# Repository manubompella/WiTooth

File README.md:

# WiTooth

The WiTooth is based on Espressif ESP32 WiFi-BT-BLE SoC (System on Chip), ESP32 contains two low-power Xtensa® 32-bit LX6 microprocessors running at 80 MHz. Features include:

 * Integrated 802.11 BGN WiFi transceiver
 * Integrated dual-mode Bluetooth (classic and BLE)
 * Dual-core Tensilica LX6 microprocessor
 * Up to 240MHz clock frequency
 * 520kB internal SRAM
 * 10-electrode capacitive touch support
 * Hardware accelerated encryption (AES, SHA2, ECC, RSA-4096)
 * 2.2 to 3.6V operating range
 * 2.5 µA deep sleep current
 * 3 SPI, 2 I2C, 2 UART
 * 16 PWM outputs
 * 2 DAC
 * 2 I2S
 * 18 analog-to-digital converter (ADC) channels
 
## Platform Features

 * Compatible with Arduino IDE
 * USB powered
 * CP2102 USB-to-UART Bridge
 * Extended breadboard compatible headers
 * UART, SPI, I2C
 * On-board RESET
 
## Maintainers

The WiTooth is maintained by thingTronics Innovations.

Main contributor:
 * Manohar Bompella@<manohar.bompella@thingtronics.com>
 * Poornima Nagesh @<poornima.nagesh@thingtronics.com>
 * Lovelesh Patel @<lovelesh.patel@thingtronics.com>

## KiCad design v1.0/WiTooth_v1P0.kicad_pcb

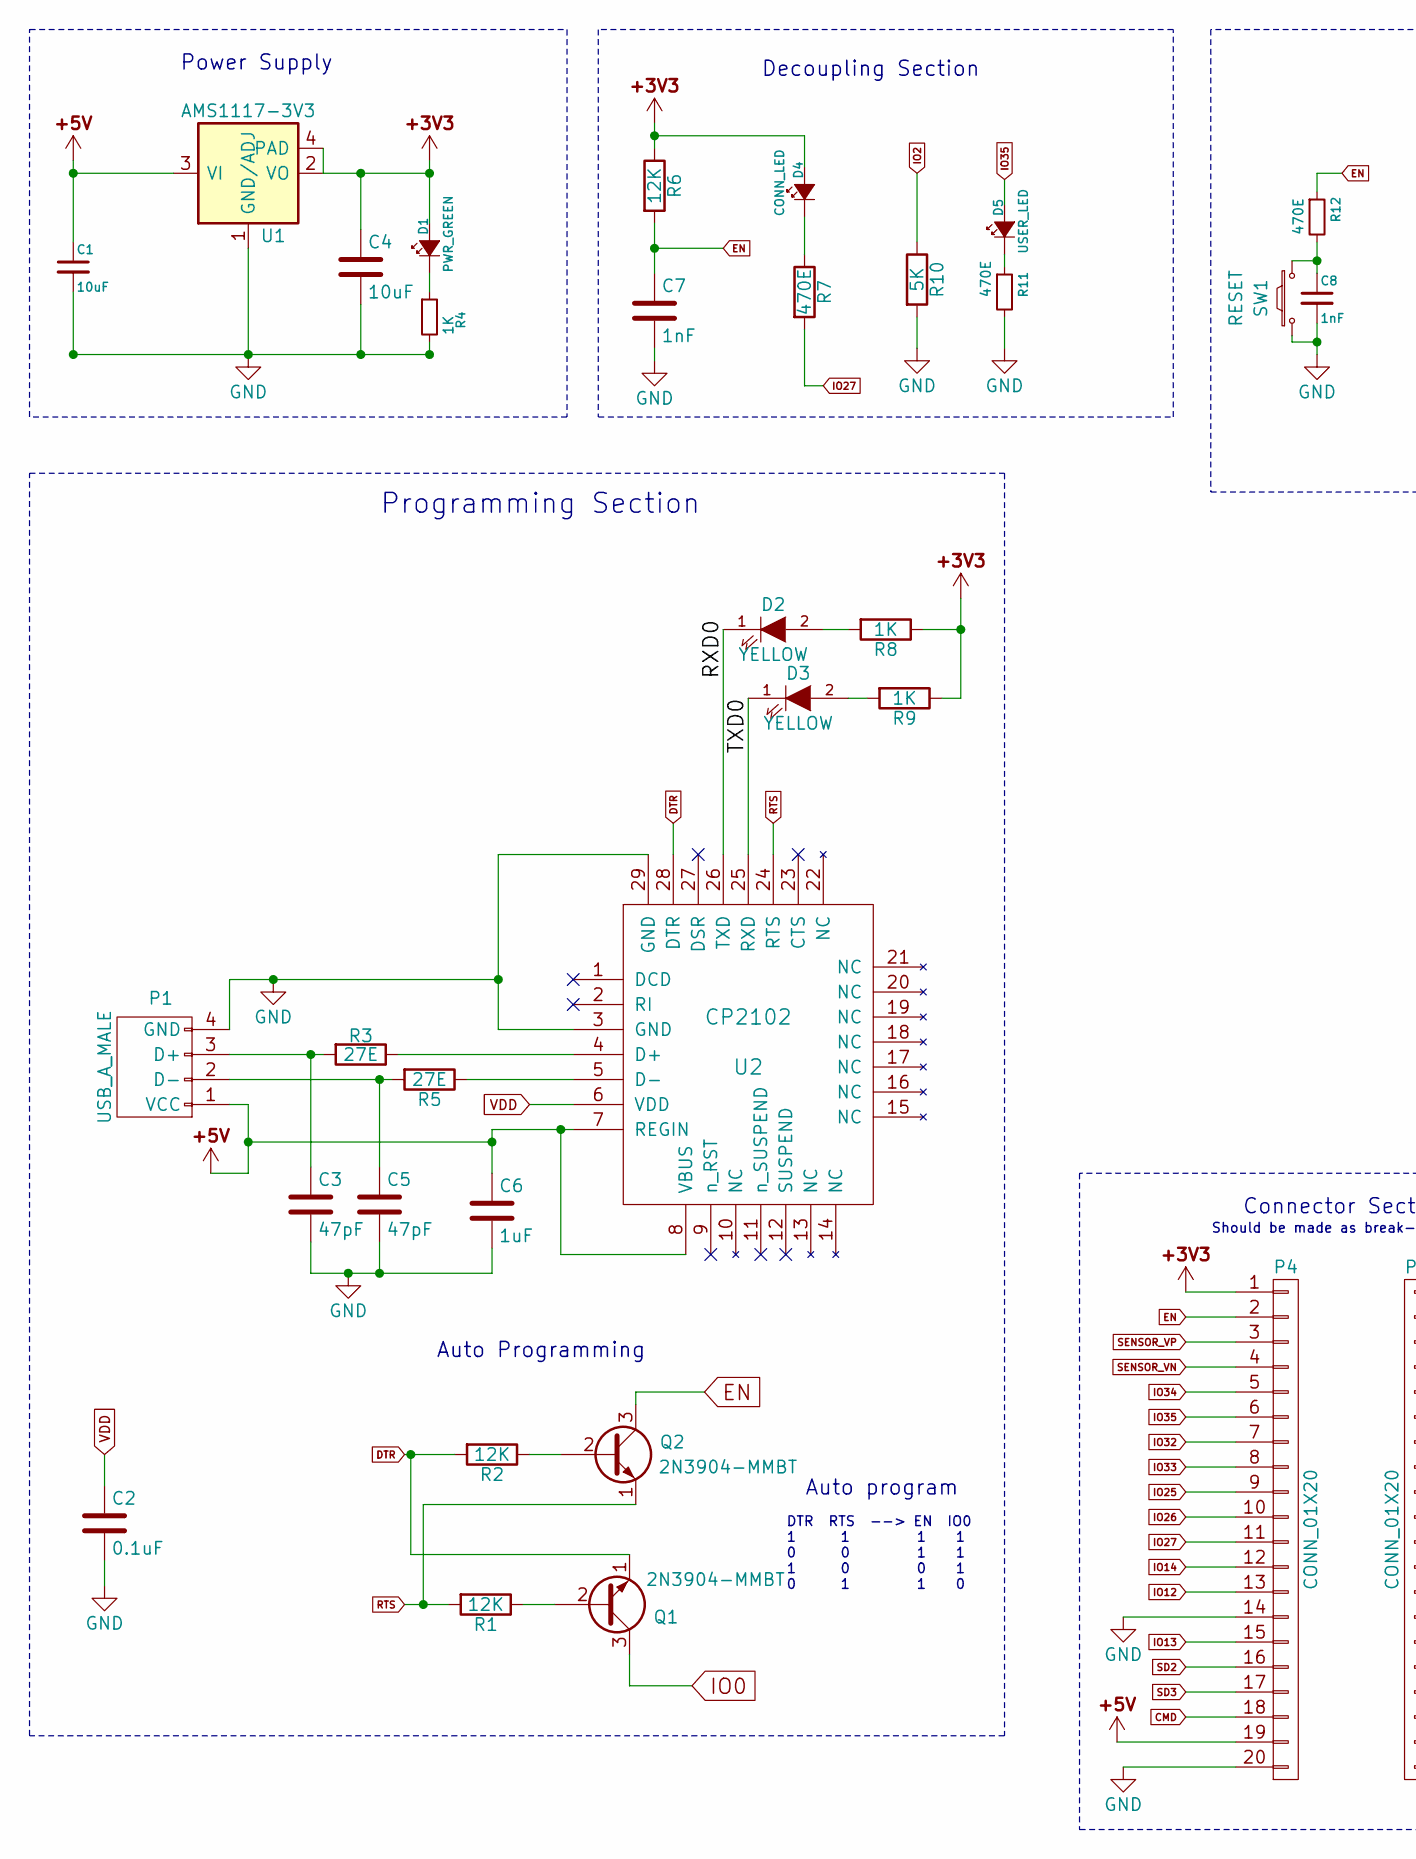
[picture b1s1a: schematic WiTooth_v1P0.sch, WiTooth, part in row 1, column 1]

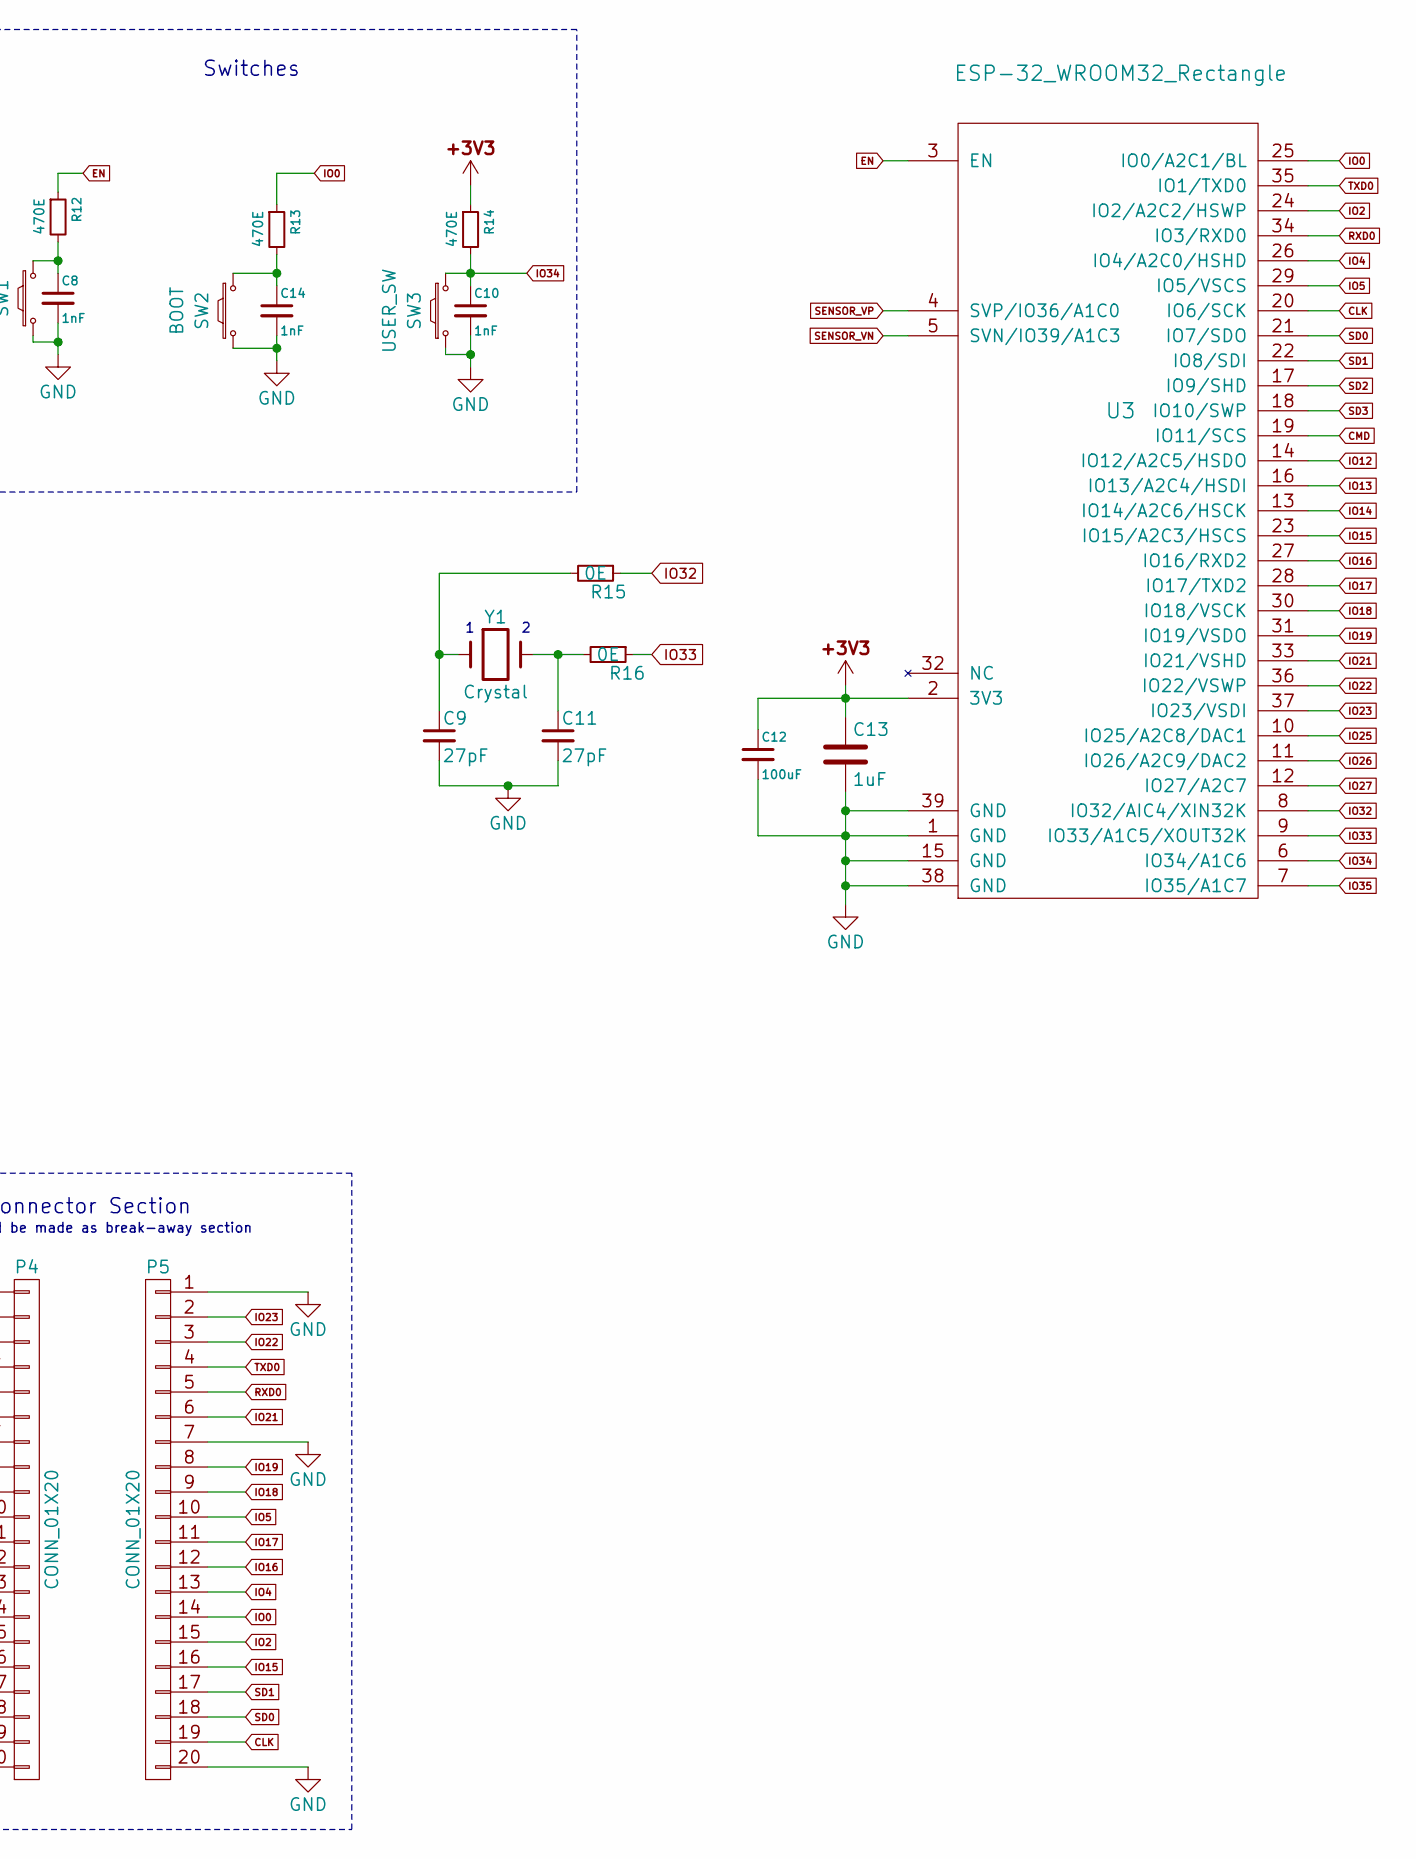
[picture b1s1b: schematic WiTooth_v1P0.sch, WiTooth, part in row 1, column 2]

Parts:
C1, C4: 10uF; C_0805_HandSoldering
C2: 0.1uF; C_0805_HandSoldering
C3, C5: 47pF; C_0805_HandSoldering
C6, C13: 1uF; C_0805_HandSoldering
C7, C8, C10, C14: 1nF; C_0805_HandSoldering
C9, C11: 27pF; C_0805_HandSoldering
C12: 100uF; C_1206_HandSoldering
D1: PWR_GREEN; LED_0805
D2, D3: YELLOW; LED_0805
D4: CONN_LED; LED_0805
D5: USER_LED; LED_0805
P1: USB_A_MALE; usb-PCB_male; MPN *********
P4, P5: CONN_01X20; Pin_Header_Straight_1x20_Pitch2.54mm
Q1, Q2: 2N3904-MMBT; SOT-23_Handsoldering
R1, R2, R6: 12K; R_0805_HandSoldering
R3, R5: 27E; R_0805_HandSoldering
R4, R8, R9: 1K; R_0805_HandSoldering
R7, R11, R12, R13, R14: 470E; R_0805_HandSoldering
R10: 5K; R_0805_HandSoldering
R15, R16: 0E; R_0805_HandSoldering
SW1: RESET; SW_SPST_B3U-1000P_SUNROM
SW2: BOOT; SW_SPST_B3U-1000P_SUNROM
SW3: USER_SW; SW_SPST_B3U-1000P_SUNROM
U1: AMS1117-3V3; SOT-223; MPN LM1117
U2: CP2102; QFN-28-1EP_5x5mm_Pitch0.5mm
U3: ESP-32_WROOM32_Rectangle; ESP32-WROOM_SMALLER_FOOTPRINT
Y1: Crystal; Crystal_SMD_0603-2pin_6.0x3.5mm_HandSoldering

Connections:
+3V3: C4.1, C12.1, C13.1, D1.2 (A), D4.2 (A), P4.1, R6.1, R8.1, R9.1, R14.1, U1.2 (VO), U1.4 (PAD), U3.2 (3V3)
+5V: C1.1, C6.1, P1.1 (VCC), P4.19, U1.3 (VI), U2.7 (REGIN), U2.8 (VBUS)
CLK: P5.19, U3.20 (IO6/SCK)
CMD: P4.18, U3.19 (IO11/SCS)
DTR: Q1.1 (E), R2.2, U2.28 (DTR)
EN: C7.1, P4.2, Q2.3 (C), R6.2, R12.1, U3.3 (EN)
GND: C1.2, C2.2, C3.2, C4.2, C5.2, C6.2, C7.2, C8.2, C9.2, C10.2, C11.2, C12.2, C13.2, C14.2, P1.4 (GND), P4.14, P4.20, P5.1, P5.7, P5.20, R4.2, R10.2, R11.2, SW1.1, SW2.1, SW3.1, U1.1 (GND/ADJ), U2.3 (GND), U2.29 (GND), U3.1 (GND), U3.15 (GND), U3.38 (GND), U3.39 (GND)
IO0: P5.14, Q1.3 (C), R13.1, U3.25 (IO0/A2C1/BL)
IO2: P5.15, R10.1, U3.24 (IO2/A2C2/HSWP)
IO4: P5.13, U3.26 (IO4/A2C0/HSHD)
IO5: P5.10, U3.29 (IO5/VSCS)
IO12: P4.13, U3.14 (IO12/A2C5/HSDO)
IO13: P4.15, U3.16 (IO13/A2C4/HSDI)
IO14: P4.12, U3.13 (IO14/A2C6/HSCK)
IO15: P5.16, U3.23 (IO15/A2C3/HSCS)
IO16: P5.12, U3.27 (IO16/RXD2)
IO17: P5.11, U3.28 (IO17/TXD2)
IO18: P5.9, U3.30 (IO18/VSCK)
IO19: P5.8, U3.31 (IO19/VSDO)
IO21: P5.6, U3.33 (IO21/VSHD)
IO22: P5.3, U3.36 (IO22/VSWP)
IO23: P5.2, U3.37 (IO23/VSDI)
IO25: P4.9, U3.10 (IO25/A2C8/DAC1)
IO26: P4.10, U3.11 (IO26/A2C9/DAC2)
IO27: P4.11, R7.2, U3.12 (IO27/A2C7)
IO32: P4.7, R15.1, U3.8 (IO32/AIC4/XIN32K)
IO33: P4.8, R16.1, U3.9 (IO33/A1C5/XOUT32K)
IO34: C10.1, P4.5, R14.2, SW3.2, U3.6 (IO34/A1C6)
IO35: D5.2 (A), P4.6, U3.7 (IO35/A1C7)
unnamed: C3.1, P1.3 (D+), R3.2
unnamed: C5.1, P1.2 (D-), R5.2
unnamed: C8.1, R12.2, SW1.2
unnamed: C9.1, R15.2, Y1.1
unnamed: C11.1, R16.2, Y1.2
unnamed: C14.1, R13.2, SW2.2
unnamed: D1.1 (K), R4.1
unnamed: D2.2 (A), R8.2
unnamed: D3.2 (A), R9.2
unnamed: D4.1 (K), R7.1
unnamed: D5.1 (K), R11.1
unnamed: Q1.2 (B), R1.1
unnamed: Q2.2 (B), R2.1
unnamed: R3.1, U2.4 (D+)
unnamed: R5.1, U2.5 (D-)
RTS: Q2.1 (E), R1.2, U2.24 (RTS)
RXD0: D2.1 (K), P5.5, U2.26 (TXD), U3.34 (IO3/RXD0)
SD0: P5.18, U3.21 (IO7/SDO)
SD1: P5.17, U3.22 (IO8/SDI)
SD2: P4.16, U3.17 (IO9/SHD)
SD3: P4.17, U3.18 (IO10/SWP)
SENSOR_VN: P4.4, U3.5 (SVN/IO39/A1C3)
SENSOR_VP: P4.3, U3.4 (SVP/IO36/A1C0)
TXD0: D3.1 (K), P5.4, U2.25 (RXD), U3.35 (IO1/TXD0)
VDD: C2.1, U2.6 (VDD)

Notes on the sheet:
Switches
Power Supply
Connector Section
Decoupling Section
Should be made as break-away section
Programming Section
Auto Programming
Auto program
DTR RTS --> EN IO0 1 1 1 1 0 0 1 1 1 0 0 1 0 1 1 0

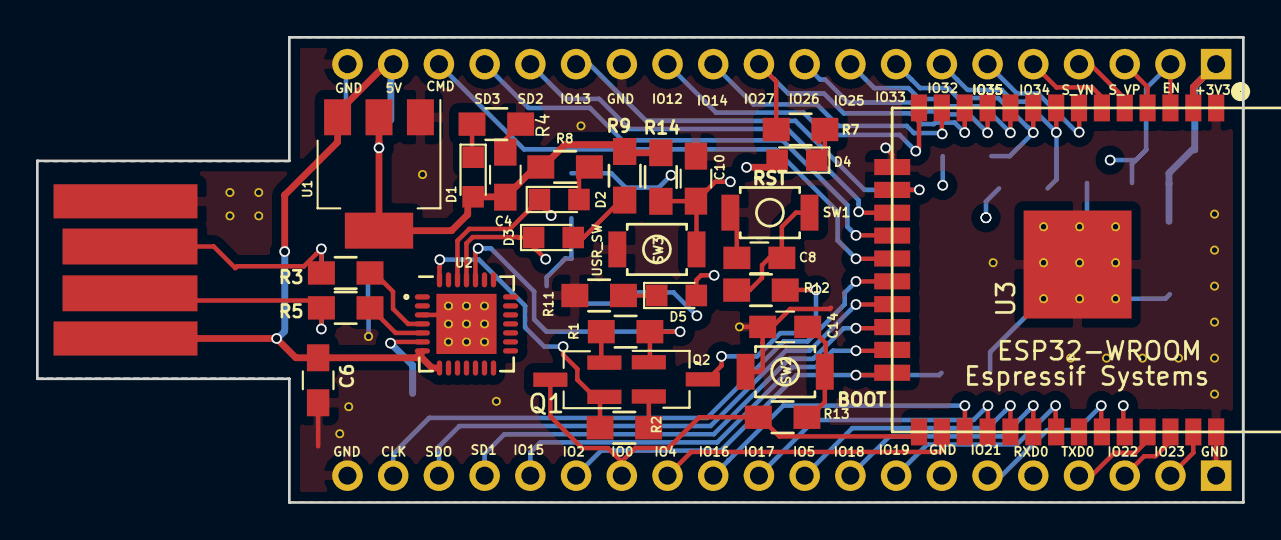
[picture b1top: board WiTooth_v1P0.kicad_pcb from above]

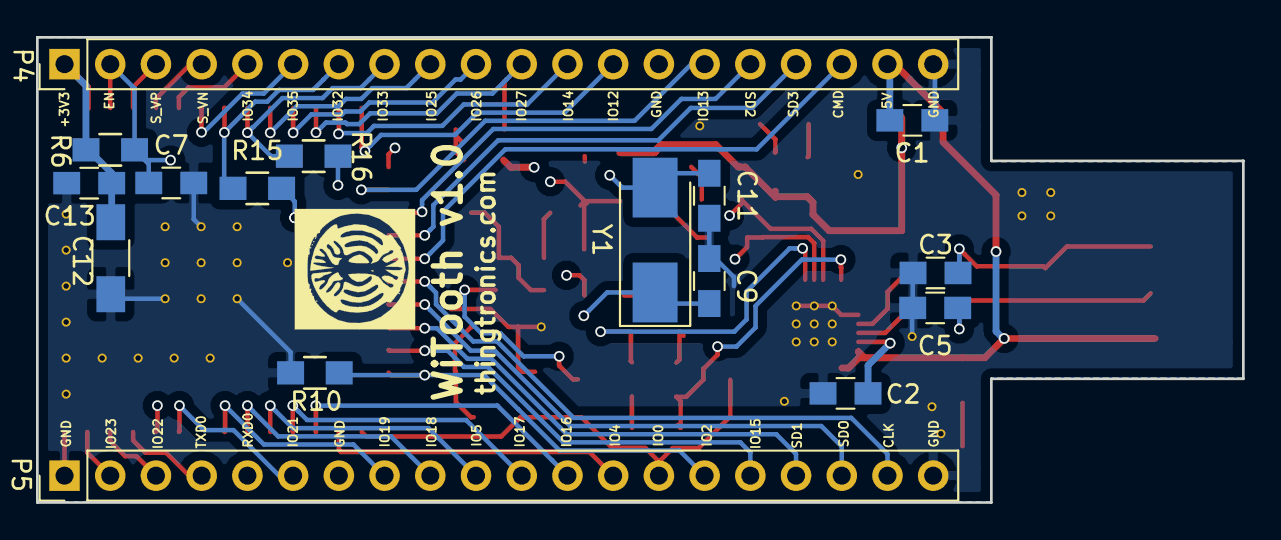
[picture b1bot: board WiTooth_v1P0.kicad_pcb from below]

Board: 4 copper layers, 67.0 x 25.8 mm, 47 parts (16 on the bottom side), 54 nets.

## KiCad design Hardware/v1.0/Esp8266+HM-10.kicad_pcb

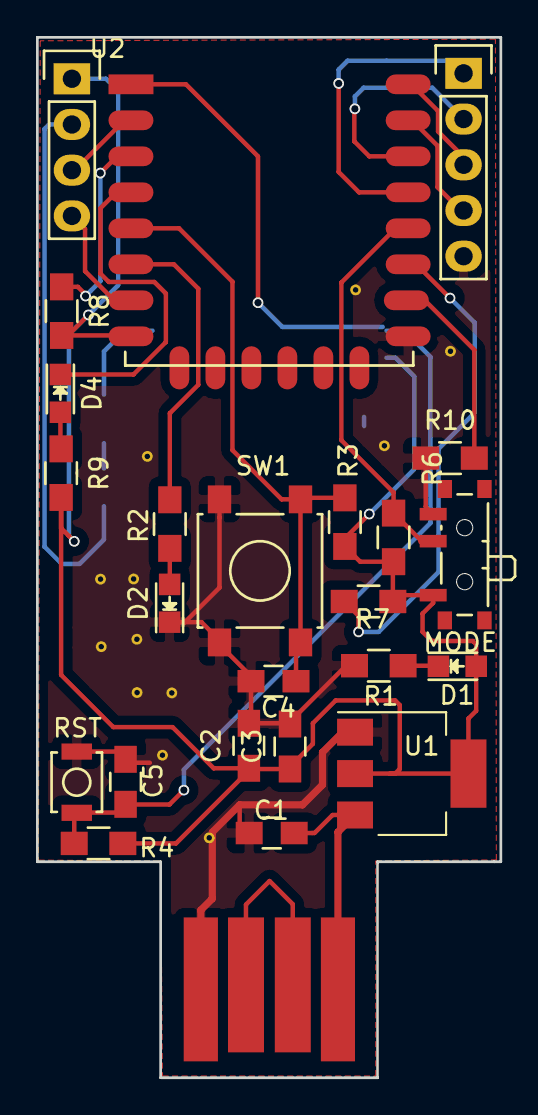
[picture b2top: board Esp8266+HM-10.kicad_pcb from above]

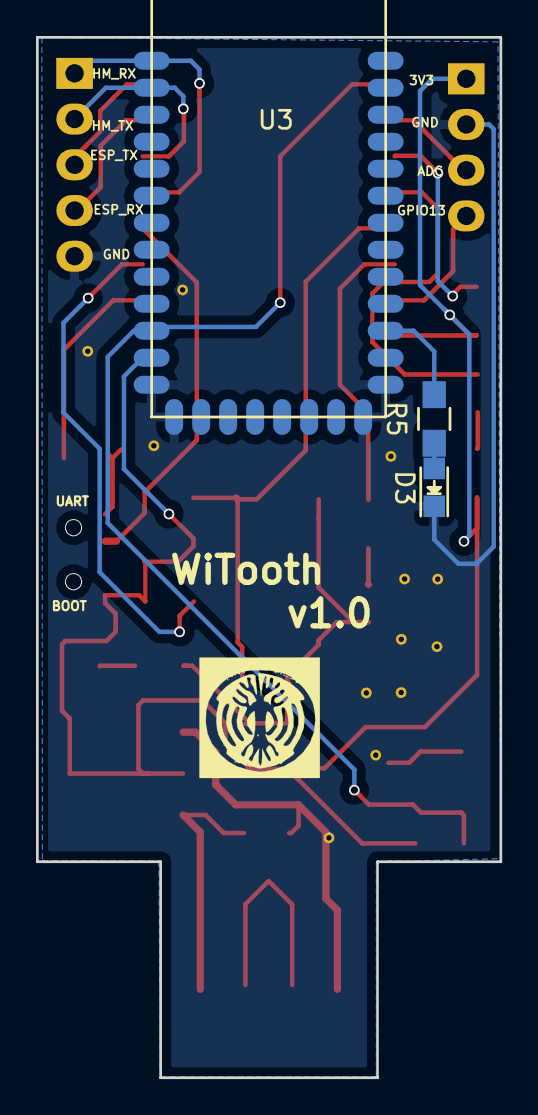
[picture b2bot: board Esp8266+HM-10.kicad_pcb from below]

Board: 2 copper layers, 25.8 x 57.8 mm, 26 parts (3 on the bottom side), 19 nets.

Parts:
C1, C3: 0.1uF; C_0805_HandSoldering
C2: 10uF; C_0805_HandSoldering
C4, C5: 15nF; C_0805_HandSoldering
D1: Power; LED_0805
D2: BUTTON_LED; LED_0805
D3: HM10_LED; LED_0805
D4: CONN_LED; LED_0805
MODE: Mode; SW_SPDT_PCM12
P1: USB_A; usb-PCB_male
R1, R2, R5, R9: 470E; R_0805_HandSoldering
R3, R4, R6, R7, R8, R10: 12K; R_0805_HandSoldering
RST: RST_SW; SW_SPST_B3U-1000P
SW1: USER_SW; SW_SPST_B3S-1000
U1: AMS1117-3V3; SOT-223
U2: ESP-12E
U3: HM-10; HM10_footprint

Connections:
+3V3: C2.1, C3.1, D1.2, MODE.1, R3.1, R4.1, R6.2, R7.2, R8.2, R9.2, U1.2, U1.4, U2.8, U3.12
+5V: C1.1, P1.1, U1.3
CH_PD: R8.1, U2.3
GND: C1.2, C2.2, C3.2, C4.2, C5.2, D2.1, D3.1, MODE.3, P1.4, R1.2, R10.1, RST.1, SW1.1, U1.1, U2.9, U3.13, U3.14, U3.21, U3.22
GPIO0: MODE.2, R6.1, U2.e12
GPIO2: R7.1, U2.11
GPIO12: R2.1, U2.6
GPIO14: C4.1, R3.2, SW1.2, U2.5
GPIO15: R10.2, U2.10
GPIO16: D4.1, U2.4
HM_RESET: C5.1, R4.2, RST.2, U2.1, U3.11
HM_RX: U2.13, U3.1
HM_TX: U2.14, U3.2
unnamed: D1.1, R1.1
unnamed: D2.2, R2.2
unnamed: D3.2, R5.1
unnamed: D4.2, R9.1
unnamed: P1.2, P1.3
unnamed: R5.2, U3.24

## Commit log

2016-12-12 Added Schematic , foot prints and layout
2016-12-14 Schematic and layout changed
    - Schematic
    i removed 2x4 header and added 1x5 ,1x4 header
    - layout changed
2017-02-05 Schematic and Reference files Added
    Schematic ,
    Reference files Added
2017-02-05 updated schematic
    - added cp2102
    - added come extra redundancy
2017-02-08 schematic half verified; footprint association done
2017-02-08 all changes done; schematic verified
2017-02-08 initial placement started
2017-02-09 basic placement done
2017-02-12 schematic updated and some parts removed; layout work started
2017-02-15 Routing completed for all
    Routing completed for all
2017-02-17 BOM generated and Routing Done
    - Bom generated
    - Routing Completed
    - Silk Screen Added
2017-11-13 read me changes
    read me changes
